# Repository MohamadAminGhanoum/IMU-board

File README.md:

# IMU-board
Im making a module that has small sensors on the pcbs, which will give me motion data, which i will track and recieve on either my phone or computer using the usb-c. i have planned to use components to measure acceleration, and gestures, etc. i have done some research, and i have decided to use the ST ISM330DHCXTR which can be found from LCSC electronics.
I want for instance to test this when im inside the car, and i want to see what data it will provide me, and whether it is accurate compared to my phone (and possibly whether my phone is accurate compared with it ;).

## Schematics:

## PCB

## BOM

|Id |Name             |Footprint                                              |Quantity                 |Price |Value                      |Supplier    |LINK:                                                                                                                                                                                                                                   |
|---|-----------------|-------------------------------------------------------|-------------------------|------|---------------------------|------------|----------------------------------------------------------------------------------------------------------------------------------------------------------------------------------------------------------------------------------------|
|1  |SW2              |SW_SPST_TS-1088-xR020                                  |1                        |0     |enable                     |Self-sourced|                                                                                                                                                                                                                                        |
|2  |SW1              |SW_SPST_TS-1088-xR020                                  |1                        |0     |boot                       |Self-sourced|                                                                                                                                                                                                                                        |
|3  |R5,R4            |R_0603_1608Metric                                      |2                        |0     |33r                        |Self-sourced|                                                                                                                                                                                                                                        |
|4  |U3               |ESP32-S3-WROOM-1                                       |1                        |5.53  |ESP32-S3-WROOM-1           |LCSC        |https://www.lcsc.com/product-detail/C2913202.html?s_z=n_q_p_ESP32%2520S3%2520WROOM&spm=wm.ssy.bg.3.stp&lcsc_vid=EQBXBlEAQgcKBVQCEVVYVVZWFAJcV1dXFlJYUFxeRgIxVlNeRFVfX1xXQlhfVTsOAxUeFF5JWBYZEEoKFBINSQcJGk4NBhADEA4cHktTQVFADxALGw%3D%3D|
|5  |U2               |SOT-223-3_TabPin2                                      |1                        |1     |AMS1117-3.3                |LCSC        |https://www.lcsc.com/product-detail/C6186.html?spm=wm.gwc.xh.1.tp___wm.sxq.ssl.gwc&lcsc_vid=EQBXBlEAQgcKBVQCEVVYVVZWFAJcV1dXFlJYUFxeRgIxVlNeRFVfX1xXQlhfVTsOAxUeFF5JWBYZEEoKFBINSQcJGk4NBhADEA4cHktTQVFADxALGw%3D%3D                    |
|6  |U1               |LGA-14_3x2.5mm_P0.5mm_LayoutBorder3x4y                 |1                        |6.28  |ISM330DHCX                 |LCSC        |https://www.lcsc.com/product-detail/C2655101.html?spm=wm.gwc.xh.0.tp___wm.sxq.ssl.gwc&lcsc_vid=EQBXBlEAQgcKBVQCEVVYVVZWFAJcV1dXFlJYUFxeRgIxVlNeRFVfX1xXQlhfVTsOAxUeFF5JWBYZEEoKFBINSQcJGk4NBhADEA4cHktTQVFADxALGw%3D%3D                 |
|7  |R6               |R_0603_1608Metric                                      |1                        |0     |1k                         |Self-sourced|                                                                                                                                                                                                                                        |
|8  |R3               |R_0603_1608Metric                                      |1                        |0     |10k                        |Self-sourced|                                                                                                                                                                                                                                        |
|9  |R2,R1            |R_0603_1608Metric                                      |2                        |0     |5.1k                       |Self-sourced|                                                                                                                                                                                                                                        |
|10 |J1               |USB_C_Receptacle_GCT_USB4105-xx-A_16P_TopMnt_Horizontal|1                        |0     |USB_C_Receptacle_USB2.0_14P|self-sourced|                                                                                                                                                                                                                                        |
|11 |D1               |C_0603_1608Metric                                      |1                        |0     |LED                        |self-sourced|                                                                                                                                                                                                                                        |
|12 |C8,C7,C6,C5,C4,C3|C_0603_1608Metric                                      |6                        |0     |100nF                      |self-sourced|                                                                                                                                                                                                                                        |
|13 |C2               |C_0603_1608Metric                                      |1                        |0     |22 uF                      |self-sourced|                                                                                                                                                                                                                                        |
|14 |C1               |C_0603_1608Metric                                      |1                        |0     |10 uF                      |self-sourced|                                                                                                                                                                                                                                        |
|15 |PCB              |                                                       |                         |6     |                           |JLCPCB      |                                                                                                                                                                                                                                        |
|   |                 |                                                       |                         |      |                           |            |                                                                                                                                                                                                                                        |
|   |                 |                                                       |Total cost with shipping:|36 USD|                           |            |                                                                                                                                                                                                                                        |

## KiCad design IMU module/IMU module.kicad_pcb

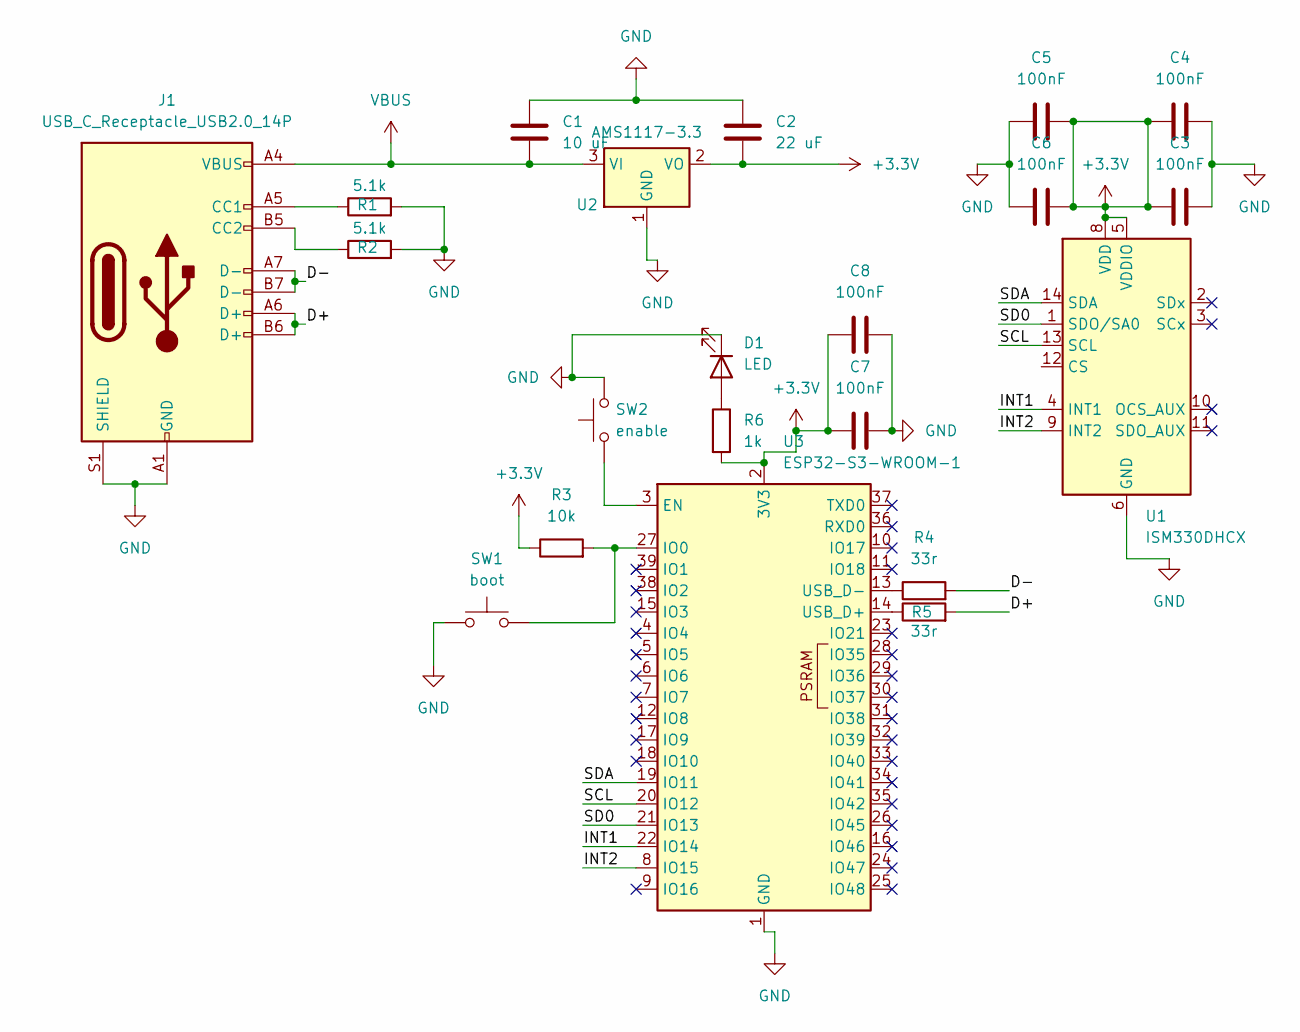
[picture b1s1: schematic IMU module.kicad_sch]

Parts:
C1: 10 uF; C_0603_1608Metric
C2: 22 uF; C_0603_1608Metric
C3, C4, C5, C6, C7, C8: 100nF; C_0603_1608Metric
D1: LED; C_0603_1608Metric
J1: USB_C_Receptacle_USB2.0_14P; USB_C_Receptacle_GCT_USB4105-xx-A_16P_TopMnt_Horizontal
R1, R2: 5.1k; R_0603_1608Metric
R3: 10k; R_0603_1608Metric
R4, R5: 33r; R_0603_1608Metric
R6: 1k; R_0603_1608Metric
SW1: boot; SW_SPST_TS-1088-xR020
SW2: enable; SW_SPST_TS-1088-xR020
U1: ISM330DHCX; LGA-14_3x2.5mm_P0.5mm_LayoutBorder3x4y
U2: AMS1117-3.3; SOT-223-3_TabPin2
U3: ESP32-S3-WROOM-1

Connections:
+3.3V: C2.2, C3.1, C4.1, C5.2, C6.2, C7.1, C8.1, R3.1, R6.2, U1.5 (VDDIO), U1.8 (VDD), U2.2 (VO), U3.2 (3V3)
/D+: J1.A6 (D+), J1.B6 (D+), R5.2
/D-: J1.A7 (D-), J1.B7 (D-), R4.2
/INT1: U1.4 (INT1), U3.22 (IO14)
/INT2: U1.9 (INT2), U3.8 (IO15)
/SCL: U1.13 (SCL), U3.20 (IO12)
/SD0: U1.1 (SDO/SA0), U3.21 (IO13)
/SDA: U1.14 (SDA), U3.19 (IO11)
GND: C1.1, C2.1, C3.2, C4.2, C5.1, C6.1, C7.2, C8.2, D1.1 (K), J1.A1 (GND), J1.A12 (GND), J1.B1 (GND), J1.B12 (GND), J1.S1 (SHIELD), R1.2, R2.2, SW1.1, SW2.2, U1.6 (GND), U1.7 (GND), U2.1 (GND), U3.1 (GND), U3.40 (GND), U3.41 (GND)
unnamed: D1.2 (A), R6.1
unnamed: J1.A5 (CC1), R1.1
unnamed: J1.B5 (CC2), R2.1
unnamed: SW2.1, U3.3 (EN)
unnamed: R3.2, SW1.2, U3.27 (IO0)
unnamed: R5.1, U3.14 (USB_D+)
unnamed: R4.1, U3.13 (USB_D-)
VBUS: C1.2, J1.A4 (VBUS), J1.A9 (VBUS), J1.B4 (VBUS), J1.B9 (VBUS), U2.3 (VI)

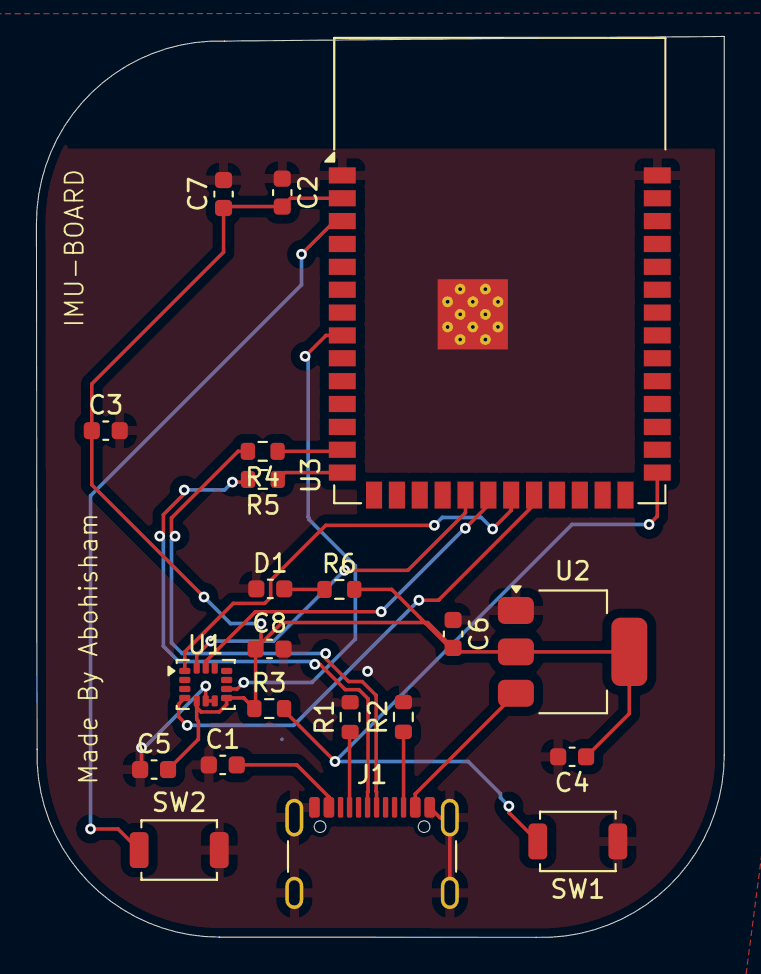
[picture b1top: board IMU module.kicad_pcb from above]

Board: 2 copper layers, 38.2 x 50.0 mm, 21 parts (0 on the bottom side), 17 nets.

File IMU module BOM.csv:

Id,Name,Footprint,Quantity,Price,Value,Supplier,LINK:
1,SW2,SW_SPST_TS-1088-xR020,1,0,enable,Self-sourced,
2,SW1,SW_SPST_TS-1088-xR020,1,0,boot,Self-sourced,
3,"R5,R4",R_0603_1608Metric,2,0,33r,Self-sourced,
4,U3,ESP32-S3-WROOM-1,1,5.53,ESP32-S3-WROOM-1,LCSC,https://www.lcsc.com/product-detail/C2913202.html?s_z=n_q_p_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
5,U2,SOT-223-3_TabPin2,1,1,AMS1117-3.3,LCSC,https://www.lcsc.com/product-detail/C6186.html?spm=wm.gwc.xh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
6,U1,LGA-14_3x2.5mm_P0.5mm_LayoutBorder3x4y,1,6.28,ISM330DHCX,LCSC,https://www.lcsc.com/product-detail/C2655101.html?spm=wm.gwc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
7,R6,R_0603_1608Metric,1,0,1k,Self-sourced,
8,R3,R_0603_1608Metric,1,0,10k,Self-sourced,
9,"R2,R1",R_0603_1608Metric,2,0,5.1k,Self-sourced,
10,J1,USB_C_Receptacle_GCT_USB4105-xx-A_16P_TopMnt_Horizontal,1,0,USB_C_Receptacle_USB2.0_14P,self-sourced,
11,D1,C_0603_1608Metric,1,0,LED,self-sourced,
12,"C8,C7,C6,C5,C4,C3",C_0603_1608Metric,6,0,100nF,self-sourced,
13,C2,C_0603_1608Metric,1,0,22 uF,self-sourced,
14,C1,C_0603_1608Metric,1,0,10 uF,self-sourced,
15,PCB,,,6,,JLCPCB,
,,,,,,,
,,,Total cost with shipping:,36 USD,,,
